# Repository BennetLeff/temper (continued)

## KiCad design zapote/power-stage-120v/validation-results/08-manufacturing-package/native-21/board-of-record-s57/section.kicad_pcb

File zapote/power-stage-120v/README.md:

# power-stage-120v: full-bridge induction power stage

> **Stale header (audit 2026-10-20):** the status and design text below predate the s53 board. Current: board s57 (25596d8e; FET holes 1.8 mm; `validation-results/08-manufacturing-package/native-21/fab/FAB-NOTE.md`), 290 × 190 mm, 2EDR8259X drivers, CA-IS3720HW isolators, PS1 deleted, KLDR025.TXP fuse, CT 1:200, U47 Schmitt buffer before U13.A. See DECISIONS.md items 75 and later (s54: item 81; s55: item 82; s56: item 85).

Status: **source compiled and audited; 240 × 160 mm four-layer placement
generated; native-06 routed and checked for renewed D4 review; physical NOT RUN.**
Design basis and justification: `docs/hardware/power-section-120v/` (POWER-SECTION.md,
LOSS-REFACTOR.md, COIL-MC.md). Front-end decision: `docs/adr/2026-09-25-front-end-architecture-brief.md`.

One board carries the mains entry, EMI filter, bridge rectifier and film bus, the full
bridge with both 2EDR8259X drivers next to the MOSFETs, the resonant capacitor bank and tank
current transformer, the DC-bus shoot-through OCP, isolated bus-voltage sense, the
thermal-cutoff-gated gate supply, and the SELV 15 V supply. The SELV controller (ESP32 plus the
integrated interlock, thermal-sense and RTD front end) connects through one SELV header (J4). Tank
over-current sensing is on this board (T1, U10–U13 → bus_fault); zapote/current-sense is a
bench-qualification unit only.

Native construction records: [progress](BUILD-PROGRESS.md),
[toolchain](TOOLCHAIN.md), [local footprints](FOOTPRINTS.md),
[earlier native results](NATIVE-02.md), [current routing](ROUTING.md),
[placement review](PLACEMENT-REVIEW.md), [oracle assessment](ORACLE-REVIEW.md),
[placement decisions](DECISIONS.md),
[return-current rules](RETURN-PATHS.md), and
[insulation preflight](RULES-PREFLIGHT.md). The revised 240 × 160 mm outline
and four layers are approved; the revised placement needs renewed D4 review.
D5 conditionally permits an 8.0 mm placement floor on
verified group IIIa-or-better laminate with one functional PE bond; insulation
qualification and airflow remain open. See [D5 basis](D5-BASIS.md).

## Build and verify

```sh
cd zapote/power-stage-120v
# 1. Compile (writes build/, which is gitignored)
uv tool run --offline --from "atopile==0.2.69" ato --non-interactive build \
    elec/src/power_stage_120v.ato:PowerStage120V
# 2. Per-instance part identity (vendored from harness-lab)
uv tool run --offline --from "atopile==0.2.69" python tools/circuit_export.py \
    "$PWD" "$PWD/build/resolved-components.json" \
    --entry-file elec/src/power_stage_120v.ato --entry PowerStage120V
# 3. Audit the fresh build, then (after a reviewed source change) freeze it
rustc --edition=2021 -O audit.rs -o /tmp/ps_audit
/tmp/ps_audit build/default.net build/default.csv build/resolved-components.json
cp build/default.net build/default.csv build/resolved-components.json frozen/
# 4. Mutation tests run against the frozen copies
rustc --edition=2021 --test audit.rs -o /tmp/ps_audit_t && /tmp/ps_audit_t
```

`frozen/` holds the reviewed build outputs. The netlist and resolved export embed absolute
source paths, so a rebuild elsewhere differs only in those paths. The netlist and BOM were
byte-identical, after path normalization, between two independent source snapshots (see the receipt).
`build-receipt.json` pins the hashes. Current result: 114 components, 75 nets. The audit
passes, and 48/48 tests pass, including deliberate miswires and the reference-bias regression.

**Part identity comes from `resolved-components.json` and the CSV, never from `default.net`.**
Atopile 0.2.69 writes a footprint-aliased part into the netlist's libsource field. In this
build, every 0603 resistor appears as `RC0603FR-071KL` and the LM4040 as `AO3400A`. The CSV BOM
and the per-instance resolved export are correct, and the audit cross-checks them for every
designator. `tools/circuit_export.py` is a verbatim copy of `harness-lab/circuit_export.py`
from `archive/rev38-power-entry-2026-09-25`.

## Fault interface

J4.10 now provides **BUS_FAULT**, low when both comparators are healthy and
high on either trip. U8 is a NAND; U9 is the default-high CA-IS3720HW.
This matches [the interlock's](../interlock/INTERFACES.md) active-high fault
contract without a polarity adapter. Input-side power loss defaults high
only with the output supply valid. HOT5 brownout, controller-supply loss,
return-wire faults and complete shutdown timing remain unqualified; see
[FAULT-INTERFACE.md](FAULT-INTERFACE.md).

## Controller header J4 (Molex Micro-Fit 3.0, 2x8, SELV)

| Pin | Net | Direction / meaning |
| ---: | --- | --- |
| 1 | BIAS_GOOD_J4 | Out: BIAS_GOOD (U40) through R146 220 k, high while the bias monitors are good and the heartbeat runs (stage 48, OPEN-ITEMS B13 H2). The controller must read it high-Z (≥ 1 MΩ pull-down). Was V15_SELV (PS1) until stage 38; the controller is powered through its J13 |
| 2, 4, 15 | SELV_GND | Return |
| 3 | V3V3 | In: controller 3.135–3.465 V rail matching the interlock contract; powers the SELV sides of U1, U2, U4, U9 |
| 5 / 6 | PWM_HA / PWM_LA | In: leg A high / low gate commands |
| 7 / 8 | PWM_HB / PWM_LB | In: leg B high / low (four independent signals allow phase-shift control) |
| 9 | PERMIT | In: active high. Low, floating or unpowered holds both drivers' DIS high (outputs off) |
| 10 | BUS_FAULT | Out: healthy low; high on shunt OCP (92.59 A nominal; 71.59–114.57 A at the release basis before the Kelvin shift, COMMISSIONING B2 / B3), bus OVP (272.64–287.45 V) or tank-CT over-current either polarity (73.19 A nominal, band 67.36–79.32 A, B9). U13 ORs the isolated bus fault with the tank-CT comparators on the SELV side. Fully unpowered HOT side defaults high while the controller supply is valid. |
| 11 / 12 | VBUS_P / VBUS_N | Out: AMC1311 differential output. V(P) − V(N) ≈ bus voltage / 120 (unity-gain amplifier; 198 V → 1.65 V; confirm gain and common-mode on the datasheet) |
| 13 | CT_ZC | Out: tank-current zero crossing (TLV3201 push-pull, 3.3 V logic). Undefined with no tank current: the controller must ignore it when idle |
| 14 | CT_MON | Out: biased tank-current waveform through 1 kΩ: 1.65 V + I_tank × 15 mV/A (1:200 into 3 Ω). The host input must be high impedance (≥ 10 MΩ assumed by the model) |
| 16 | LINE_ZC | Out: line zero crossing (U36 opto → U24 buffer, 3.3 V logic). Controller C49 reads it through 1 kΩ. Was SELV_GND in early stages. |

Required on the controller side (not on this board):
- the active-high-fault latch that drops PERMIT on BUS_FAULT high, tank OCP, over-temperature or a watchdog timeout
- phase control from CT_ZC that inhibits switching before the tank goes capacitive (the comparator is on this board; the inhibit logic is not)
- integration respecting the single functional PE bond implemented on this board

## Domains and barrier

HOT reference is `LEG_RET`, the leg side of the 1 mΩ shunt; layout must star it at shunt pad 2.
Only these parts may cross HOT↔SELV, and the audit enforces each pin's side:

- Infineon 2EDR8259X (U1, U2; UCC21550 until stage 28, DECISIONS 31)
- AMC1311 (U4)
- CA-IS3720HW (U9, U32)
- VOL628A-2X001T (U36, line zero-cross; mains to SELV)
- CST3015-200ED (T1)

PS1 (IRM-20-15) was deleted at stage 38. U41 / U42 (R24C2T25) and U43 / U44 (ISO6721FB) are HOT-to-HOT.

The controller return has one removable functional 0 Ω PE link. It is not
a protective-earth path and does not waive HOT-to-controller insulation.

Provisional creepage and clearance rules are applied to the routed board. The full-bridge differential
RMS and peak voltages across each barrier remain unverified; the historical
tank peak is not a sufficient basis for selecting creepage bands. See
[RULES-PREFLIGHT.md](RULES-PREFLIGHT.md).

## Safety chain implemented in hardware

| Fault | Path |
| --- | --- |
| Hard short or bridge failure | F1 25 A time-delay ceramic (Eaton Bussmann MDA-25-R: 10 kA @ 125 Vac, 1.5 kA @ 250 Vac) in 30 A 01220088Z clips |
| Shoot-through / MOSFET short | 1 mΩ DC-return shunt → TLV3201 (nominal 92.59 A) → NAND gate → CA-IS3720HW → BUS_FAULT high → interlock latch → PERMIT low → DIS |
| Elevated DC bus | Bus divider → TLV3201 (272.64–287.45 V) → NAND gate → CA-IS3720HW → BUS_FAULT high → interlock latch → PERMIT low → DIS; this inhibits restart but does not clamp bus voltage |
| Tank over-current / pan fault | CT (T1) → on-board comparators U10/U11, ORed with the bus fault in U13 → bus_fault → controller interlock latch |
| Heatsink or glass over-temperature | Off-board Microtemp cutoffs in the J3 loop open the IRM-05-15 input: gate drive and HOT 5 V drop; BUS_FAULT defaults high if controller 3.3 V remains valid. No electronics or firmware involved |
| Controller hang / reset | Interlock-board watchdog; PERMIT floating = disabled |
| Gate-supply loss | 2EDR8259X UVLO and active output clamp hold outputs low; 10 kΩ gate-source hold-off |
| Line surge | TMOV20RP175E (175 Vrms, 455 V clamp) ahead of 650 V MOSFETs |

## Open before fabrication and powered qualification

1. **Coil measurement** (COIL-MC.md). Sets the resonant bank value (0.54 µF now, for 70 µH / 32 kHz), CT burden and frequency limits.
2. **Parts to confirm against manufacturer drawings:**
   - J1 is Phoenix 1714971 (MKDS 5/2-9,5, UL/CSA group B 30 A; stage 27) for L/N only; J6 is a Phoenix 1704004 PE branch from the chassis stud. J2/J5 and the four disconnect terminals use Würth 74650074; assembly, temperature and spacing qualification remain open.
   - ~~Littelfuse 102071 clip current rating~~ (10 A): replaced by 30 A 01220088Z clips. The fuse is now Eaton Bussmann MDA-25-R (25 A, 10 kA @ 125 Vac), DECISIONS.md 2026-10-08
   - ~~TDK B82726S2203A020 pin numbering~~ (confirmed from datasheet 2026-09-25: windings 1-4, 2-3)
   - ~~Molex 0430451612 order code~~: a real, current Micro-Fit 3.0 2×8 vertical part that matches the footprint and pinout. Its mate is 43025-1600 + 43030-0007 (`validation-results/08-manufacturing-package/native-21/owner-items/order/ORDER-PACKAGE.md` §1c). Only the post-hole check against Molex drawing 430451612_sd is left
   - 942C AC voltage rating vs frequency (≈ 236 V rms at line crest, 35 kHz): CDE's 1200 Vdc curves (942C.pdf p.4) have no 0.22 µF trace. The 0.33 µF trace allows ≈ 270 V rms at 35 kHz (read from the plot), and the smaller value allows more, so it passes at 25 °C. The hot-spot rating stays a bench item
3. **Footprint qualification:** all current local footprints are now
   in `libraries/`. [FOOTPRINTS.md](FOOTPRINTS.md) records their drawing
   references and provisional formed-lead, retention and assembly limits.
4. **Under-glass cutoff rating:** needs a glass-underside temperature measurement at the 482 °F setpoint; heatsink cutoff about 120 °C, from available G4A ratings.
5. **Bench:** dead time (39 kΩ ≈ 348 ns nominal), gate resistors, snubber value, OCP trip calibration, ZVS at light load.

Physical assembly, powered test, EMI, insulation and certification: **NOT RUN**.

The release gates (two tiers: bench prototype lot vs mains-connected / product release) are in
`validation-results/08-manufacturing-package/native-21/fab/FAB-NOTE.md`. The owner decisions M6, M10
and M11 are in DECISIONS.md (2026-10-08). The integrated SELV controller that drives J4 is captured in
`zapote/controller/`.

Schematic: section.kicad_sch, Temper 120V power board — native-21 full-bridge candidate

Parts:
BR1: GBJ2510-F; Diode_Bridge_GBJ2510
C1, C2: R463N410050N1K; KEMET_R463N410000N1M_P22.50_ReviewOnly
C3, C4: DE1E3RA222MJ4BH01F; Murata_DE1E3RA222MA4BP01F_P10.0_Pad1.5_ReviewOnly
C5, C6: B32676G1905K000; TDK_B32656G0275J000_4Pin_P37.50_P20.30_ReviewOnly
C7, C14, C25, C28, C29, C32, C34, C35, C36, C37, C44, C45, C46, C47, C48, C49, C54, C61, C65, C70, C74, C75, C80, C81, C82, C87, C89, C131, C133, C134, C135, C139, C144, C153, C154, C155, C156, C157, C158, C159, C160, C161, C163, C168, C169, C170, C171, C172, C173, C174, C175, C176, C177, C178, C179: CC0603KRX7R9BB104; C_0603_1608Metric
C8, C10, C15, C17: CC0805KRX7R9BB104; C_0805_2012Metric
C9, C16, C24, C26, C90, C91, C92, C93, C94, C95, C96, C97, C98, C99, C100, C102, C103, C104, C106, C107, C108, C132, C136, C140: CL32B106KBJNNNE; C_1210_3225Metric
C11, C18: GRM21BZ71E106KE15L; C_0805_2012Metric
C12, C13, C19, C20: CC1206JKNPOCBN102; C_1206_3216Metric
C21, C22, C23, C151, C152: B32643H8104J000; Bank_Film_DualPitch_P22.5_P27.5_Radial
C27, C31, C33, C66, C67, C68, C69, C76, C77, C78, C79, C83, C84, C85, C86, C164, C165, C166: C0603C102J5GACTU; C_0603_1608Metric
C30, C167: CL10C101JB8NNNC; C_0603_1608Metric
C38, C39, C40, C41: B32652A0104K000; TDK_B32652A0104K000_P15.00_ReviewOnly
C42, C43: GRM31C5C1H104JA01L; C_1206_3216Metric
C50, C51, C52, C53, C57, C58, C59, C60, C64: GRM188R71E105KA12D; C_0603_1608Metric
C55, C56, C62, C63: GRM1885C1H472JA01D; C_0603_1608Metric
C71, C72, C105, C109, C162: CL10C331JB8NNNC; C_0603_1608Metric
C110, C111, C112, C113, C114, C115, C116, C117, C118, C119, C120, C121, C122, C123, C124, C125: CL05B104KB54PNC; C_0402_1005Metric
C126, C127, C128, C129: 6SVPC220MV; CP_Elec_6.3x5.9
C145, C146, C147, C148, C149, C150: CL21B105KBFNNNE; C_0805_2012Metric
D3, D17: 30KPA150CA; P600_Axial_P12.70mm_ReviewOnly
D4, D5: BAS116H,115; D_SOD-123F
D6, D7, D8, D9: PMEG6030EP,115; D_SOD-128
D18, D19, D20: BAT54S-7-F; SOT-23
F1: KLDR025.TXP; Fuseholder_Clip-10.3x38mm_Littelfuse_125_Inline_P41.76x10.8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
F2: 3403.0279.23; Fuse_Schurter_UMT-H_15.4x5.35mm
J1: 1714971; Phoenix_MKDS-5-2-9.52_1714971
J2, J5: 7466004R; Wuerth_REDCUBE-SMT_WP-SMBU_7466004R
J3, J11: B2P3-VH(LF)(SN); JST_VH_B2P3-VH_1x02_P7.92mm_Vertical
J4: 0430451612; Molex_Micro-Fit_3.0_43045-1612_2x08_P3.00mm_Vertical
J6: 1704004; Phoenix_KDS3_1704004_1Pos_2Pin_ReviewOnly
L1: B82726S2243A020; B82726S2_ReviewOnly
PS2: MPM-20-24; Converter_ACDC_MeanWell_IRM-20-xx_THT
Q2, Q3, Q5, Q6: IPW65R018CFD7; TO-247-3_Vertical_D1.8
R1, R2: 1206W4F1003T5E; R_1206_3216Metric
R3, R4, R146: RC1206FR-07220KL; R_1206_3216Metric
R5: CSS2H-2512R-1L00F; R_Shunt_Bourns_CSS2H-2512_Kelvin
R6, R14: 0603WAF1000T5E; R_0603_1608Metric
R7, R15, R62, R128, R135, R136, R138, R140, R142: 0603WAF1003T5E; R_0603_1608Metric
R9, R17, R133: RT0603BRD0749K9L; R_0603_1608Metric
R10, R12, R18, R20: PS122WF680JT4E; R_2512_6332Metric
R11, R13, R19, R21, R73, R76, R91, R109, R124: 0603WAF1002T5E; R_0603_1608Metric
R22, R23, R24, R25, R26, R27, R28, R29: RC1206FR-07470KL; R_1206_3216Metric
R30: RT0603BRD0715K8L; R_0603_1608Metric
R31: 0603WAF5601T5E; R_0603_1608Metric
R32, R36, R49, R50, R78, R80, R82, R84, R96, R98, R100, R102, R111, R113, R115, R117: RT0603BRD0710KL; R_0603_1608Metric
R33: RT0603BRD077K5L; R_0603_1608Metric
R34, R127, R129: RT0603BRD0716KL; R_0603_1608Metric
R35, R44, R45, R61, R86, R88, R93, R104, R106, R119, R121: RT0603BRD0711KL; R_0603_1608Metric
R37: RT0603BRD07140KL; R_0603_1608Metric
R38: 0603WAF0000T5E; R_0603_1608Metric
R39: RC1206FR-073RL; R_1206_3216Metric
R40, R41: RT0603BRD071KL; R_0603_1608Metric
R42: 1206W4F1001T5E; R_1206_3216Metric
R43, R46: RT0603BRD072K21L; R_0603_1608Metric
R47, R134: 0603WAF1001T5E; R_0603_1608Metric
R48: RT0603BRD07105KL; R_0603_1608Metric
R51, R52, R55, R56: RL1206FR-070R68L; R_1206_3216Metric
R53, R54, R57, R58: 1206W4F100KT5E; R_1206_3216Metric
R59, R63, R65: RC1206FR-072K2L; R_1206_3216Metric
R67, R68, R69, R70: RC1206FR-0716K5L; R_1206_3216Metric
R71, R72, R74, R75, R131: ERJ-PA3F4991V; R_0603_1608Metric
R77, R95, R110: RT0603BRD076K2L; R_0603_1608Metric
R79, R97, R112: RT0603BRD074K42L; R_0603_1608Metric
R81, R99, R114: RT0603BRD07750RL; R_0603_1608Metric
R83, R101, R116: RT0603BRD072K94L; R_0603_1608Metric
R85, R103, R118: RT0603BRD0790K9L; R_0603_1608Metric
R87, R105, R120: RT0603BRD07104KL; R_0603_1608Metric
R92, R94, R144: RT0603BRD0763K4L; R_0603_1608Metric
R125: 0603WAF3302T5E; R_0603_1608Metric
R130: AC05000001507JAC00; R_Axial_Vishay_AC05_D7.5mm_P5.08mm_Vertical
R132: 0603WAF2200T5E; R_0603_1608Metric
R137, R139, R141, R143: 0603WAF2702T5E; R_0603_1608Metric
R145: TNPW060311K7BEEA; R_0603_1608Metric
RV1: TMOV20RP175E; TMOV20RP_ReviewOnly
T1: CST3015-200ED; CST3015
U1, U2: 2EDR8259XXUMA1; SOIC16W_Isolated
U3, U37, U38, U39: TPS70950QDBVRQ1; SOT-23-5
U4: AMC1311BDWVR; SOIC-8_7.5x5.85mm_P1.27mm
U5: LM4050AEM3-2.5/NOPB; SOT-23
U6, U7, U10, U11, U12: TLV3201AIDBVR; SOT-23-5
U8: SN74LVC1G10DBVR; SOT-23-6
U9, U32: CA-IS3720HW; SOIC16W_DW0016B_HV
U13: SN74LVC1G332DBVR; SOT-23-6
U14: TPS3700DDCR; SOT-23-6
U15, U24, U40, U47: SN74LVC1G17DBVR; SOT-23-5
U16, U18, U20: TLVH431BQDBZR; SOT-23
U17, U19, U21: TL431BQDBZR; SOT-23
U22, U23: SN74LVC1G00DBVR; SOT-23-5
U26: TPS7A4700RGWR; Texas_RGW0020A_VQFN-20-1EP_5x5mm_P0.65mm_EP3.15x3.15mm
U29, U30, U31: LM2901BIDR; SOIC-14_3.9x8.7mm_P1.27mm
U36: VOL628A-2X001T; VOL628A_LSOP4_ReviewOnly
U41, U42: R24C2T25/R-R; RECOM_SSOP-36_7.5x12.83mm_P0.65mm_ReviewOnly
U43, U44: ISO6721FBDR; SOIC-8_3.9x4.9mm_P1.27mm
U45, U46: SN74LVC1G132DBVR; SOT-23-5

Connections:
ac_l_in: F1.1 (p1), J1.1 (p1)
ac_n_in: C1.2 (p2), J1.2 (p2), L1.2 (p2), R2.2 (p2), RV1.2 (p2)
bias_good: R146.1 (p1), U22.2 (p2), U23.2 (p2), U40.4 (Y); also elsewhere on the board
bias_good_j4: J4.1 (p1), R146.2 (p2)
bias_ha-en: R62.2 (p2), R127.1 (p1), U41.4 (p4)
bias_ha-fbm: C71.1 (p1), R92.2 (p2), R93.1 (p1), U41.33 (p33), U41.34 (p34)
bias_ha-outa_nc: U43.2 (p2)
bias_ha.iso-p3: U41.3 (p3)
bias_ha.iso-p32: U41.32 (p32)
bias_ha.monitor-good: R109.2 (p2), U30.1 (OUT2), U30.2 (OUT1), U30.13 (OUT4), U30.14 (OUT3), U43.3 (p3)
bias_ha.monitor-halfref: R97.2 (p2), R98.1 (p1), U30.5 (IN1+), U30.6 (IN2-), U30.8 (IN3-), U30.11 (IN4+)
bias_ha.monitor-ldo_en: R140.2 (p2), R141.1 (p1), U38.3 (EN)
bias_ha.monitor-ov: C77.1 (p1), R101.2 (p2), R102.1 (p1), U30.4 (IN1-); also elsewhere on the board
bias_ha.monitor-ref: R63.2 (p2), R97.1 (p1), U19.1 (K), U19.2 (REF)
bias_ha.monitor-spanov: C79.1 (p1), R105.2 (p2), R106.1 (p1), U30.10 (IN4-); also elsewhere on the board
bias_ha.monitor-spanuv: C78.1 (p1), R103.2 (p2), R104.1 (p1), U30.9 (IN3+); also elsewhere on the board
bias_ha.monitor-uv: C76.1 (p1), R99.2 (p2), R100.1 (p1), U30.7 (IN2+); also elsewhere on the board
bias_ha.monitor-v5: C136.1 (p1), C157.1 (p1), R109.1 (p1), U38.5 (OUT), U43.1 (p1)
bias_ha.monitor.ldo5-nc: U38.4 (NC)
bias_ha.split-fb: R95.2 (p2), R96.1 (p1), U18.1 (REF)
bias_hb-en: R128.2 (p2), R129.1 (p1), U42.4 (p4)
bias_hb-fbm: C72.1 (p1), R61.1 (p1), R94.2 (p2), U42.33 (p33), U42.34 (p34)
bias_hb-outa_nc: U44.2 (p2)
bias_hb.iso-p3: U42.3 (p3)
bias_hb.iso-p32: U42.32 (p32)
bias_hb.monitor-good: R124.2 (p2), U31.1 (OUT2), U31.2 (OUT1), U31.13 (OUT4), U31.14 (OUT3), U44.3 (p3)
bias_hb.monitor-halfref: R112.2 (p2), R113.1 (p1), U31.5 (IN1+), U31.6 (IN2-), U31.8 (IN3-), U31.11 (IN4+)
bias_hb.monitor-ldo_en: R142.2 (p2), R143.1 (p1), U39.3 (EN)
bias_hb.monitor-ov: C84.1 (p1), R116.2 (p2), R117.1 (p1), U31.4 (IN1-); also elsewhere on the board
bias_hb.monitor-ref: R65.2 (p2), R112.1 (p1), U21.1 (K), U21.2 (REF)
bias_hb.monitor-spanov: C86.1 (p1), R120.2 (p2), R121.1 (p1), U31.10 (IN4-); also elsewhere on the board
bias_hb.monitor-spanuv: C85.1 (p1), R118.2 (p2), R119.1 (p1), U31.9 (IN3+); also elsewhere on the board
bias_hb.monitor-uv: C83.1 (p1), R114.2 (p2), R115.1 (p1), U31.7 (IN2+); also elsewhere on the board
bias_hb.monitor-v5: C140.1 (p1), C159.1 (p1), R124.1 (p1), U39.5 (OUT), U44.1 (p1)
bias_hb.monitor.ldo5-nc: U39.4 (NC)
bias_hb.split-fb: R110.2 (p2), R111.1 (p1), U20.1 (REF)
bias_ls-fb: R77.2 (p2), R78.1 (p1), U16.1 (REF)
blw_l: F2.2 (p2), R130.1 (p1)
blw_lr: J11.1 (p1), R130.2 (p2)
bus_fault: J4.10 (p10), U13.4 (Y); also elsewhere on the board
bus_fault_flt: C167.1 (p1), R134.2 (p2), U47.2 (A)
bus_fault_hot: U8.4 (Y), U9.4 (p4); also elsewhere on the board
bus_fault_iso: R134.1 (p1), U9.13 (p13)
bus_fault_st: U13.1 (A), U47.4 (Y)
bus_p: BR1.1 (PLUS), C5.1 (p1), C5.2 (p2), C6.1 (p1), C6.2 (p2), C12.1 (p1), C19.1 (p1), C38.1 (p1), C39.1 (p1), C40.1 (p1), C41.1 (p1), D3.1 (p1), Q2.2 (D), Q5.2 (D), R3.1 (p1), R26.1 (p1)
busbleed_mid: D3.2 (p2), D17.1 (p1), R3.2 (p2), R4.1 (p1)
coil_feed: J2.1, T1.2 (p2)
crbleed_1: R22.2 (p2), R23.1 (p1)
crbleed_2: R23.2 (p2), R24.1 (p1)
crbleed_3: R24.2 (p2), R25.1 (p1)
ct_mon: J4.14 (p14), R47.2 (p2); also elsewhere on the board
ct_oc_neg: U11.1 (OUT), U13.6 (C)
ct_oc_pos: U10.1 (OUT), U13.3 (B)
ct_ref_hi: R43.2 (p2), R44.1 (p1), U10.4 (INN)
ct_ref_lo: R45.2 (p2), R46.1 (p1), U11.3 (INP)
ct_s1: C42.1 (p1), R39.1 (p1), R42.1 (p1), T1.3 (p3)
ct_s2: C42.2 (p2), C43.1 (p1), R39.2 (p2), R40.2 (p2), R41.1 (p1), T1.4 (p4), U12.4 (INN)
ct_sense_mon: D4.2 (A), D5.1 (K), R42.2 (p2), R47.1 (p1), U10.3 (INP), U11.4 (INN), U12.3 (INP)
ct_zc: J4.13 (p13), U12.1 (OUT); also elsewhere on the board
hb.iso-nc2: U32.2 (p2)
hb.iso-nc5: U32.5 (p5)
hb.iso-nc6: U32.6 (p6)
hb.iso-nc8: U32.8 (p8)
hb.iso-nc10: U32.10 (p10)
hb.iso-nc11: U32.11 (p11)
hb.iso-nc12: U32.12 (p12)
hb.iso-nc15: U32.15 (p15)
hb_bufo: R132.1 (p1), U46.4 (p4)
hb_hold: C166.1 (p1), D19.2 (p2), R133.1 (p1), U40.2 (A)
hb_m: C164.2 (p2), C165.1 (p1)
hb_rc: C162.1 (p1), R131.2 (p2), U45.2 (p2)
hb_rx: U32.13 (p13), U46.2 (p2)
hb_s: C164.1 (p1), R132.2 (p2)
hb_tx: R131.1 (p1), U32.4 (p4), U45.4 (p4)
hb_x: C165.2 (p2), D19.3 (p3)
hot5: C26.1 (p1), C28.1 (p1), C32.1 (p1), C34.1 (p1), C35.1 (p1), C36.1 (p1), C48.1 (p1), C49.1 (p1), C149.1 (p1), R31.1 (p1), R48.1 (p1), R50.1 (p1), U3.5 (OUT), U4.1 (VDD1), U6.5 (VCC), U7.5 (VCC), U8.5 (VCC), U9.3 (p3), U14.5 (VDD), U15.5 (VCC); also elsewhere on the board
hot5_en: R136.2 (p2), R137.1 (p1), U3.3 (EN)
hot5_ok_hot: U8.6 (C), U15.4 (Y)
hot5_uv_raw: R50.2 (p2), U14.1 (OUTA), U14.6 (OUTB), U15.2 (A)
hot5_uv_sense: R48.2 (p2), R49.1 (p1), U14.3 (INA)
hsb_good: R135.2 (p2), U46.1 (p1)
hv_ret: BR1.4 (MINUS), C5.3 (p3), C5.4 (p4), C6.3 (p3), C6.4 (p4), C38.2 (p2), C39.2 (p2), C40.2 (p2), C41.2 (p2), D17.2 (p2), R4.2 (p2), R5.4 (p4)
l_f: C1.1 (p1), F1.2 (p2), L1.1 (p1), R1.1 (p1), RV1.1 (p1)
l_filt: BR1.2 (AC1), C2.1 (p1), C3.1 (p1), F2.1 (p1), J3.1 (p1), L1.4 (p4), R67.1 (p1)
ldo_nr: C64.1 (p1), U26.14 (p14)
led1: R68.2 (p2), U36.1 (p1)
led2: R69.1 (p1), U36.2 (p2)
leg_a-driver_dis: R73.2 (p2), U1.5 (p5), U22.4 (p4)
leg_a-gate_h: C55.1 (p1), D6.2 (p2), Q2.1 (G), R10.2 (p2), R11.1 (p1)
leg_a-gate_l: C56.1 (p1), D7.2 (p2), Q3.1 (G), R12.2 (p2), R13.1 (p1)
leg_a-off_h: D6.1 (p1), R53.1 (p1)
leg_a-off_l: D7.1 (p1), R54.1 (p1)
leg_a-out_h: R10.1 (p1), R53.2 (p2), U1.15 (p15)
leg_a-out_l: R12.1 (p1), R54.2 (p2), U1.10 (p10); also elsewhere on the board
leg_a-permit_gate: R6.2 (p2), R7.1 (p1), U22.1 (p1)
leg_a.bias_h-damp: C126.1 (p1), R51.2 (p2)
leg_a.bias_l-damp: C127.1 (p1), R52.2 (p2)
leg_a.driver-dt: R9.1 (p1), U1.6 (p6)
leg_a.driver-nc_7: U1.7 (p7)
leg_b-driver_dis: R76.2 (p2), U2.5 (p5), U23.4 (p4); also elsewhere on the board
leg_b-gate_h: C62.1 (p1), D8.2 (p2), Q5.1 (G), R18.2 (p2), R19.1 (p1)
leg_b-gate_l: C63.1 (p1), D9.2 (p2), Q6.1 (G), R20.2 (p2), R21.1 (p1)
leg_b-off_h: D8.1 (p1), R57.1 (p1)
leg_b-off_l: D9.1 (p1), R58.1 (p1)
leg_b-out_h: R18.1 (p1), R57.2 (p2), U2.15 (p15)
leg_b-out_l: R20.1 (p1), R58.2 (p2), U2.10 (p10)
leg_b-permit_gate: R14.2 (p2), R15.1 (p1), U23.1 (p1)
leg_b.bias_h-damp: C128.1 (p1), R55.2 (p2)
leg_b.bias_l-damp: C129.1 (p1), R56.2 (p2)
leg_b.driver-dt: R17.1 (p1), U2.6 (p6)
leg_b.driver-nc_7: U2.7 (p7)
leg_ret: C13.2 (p2), C20.2 (p2), C52.1 (p1), C53.1 (p1), C56.2 (p2), C59.1 (p1), C60.1 (p1), C63.2 (p2), C92.1 (p1), C93.1 (p1), C96.1 (p1), C97.1 (p1), C114.1 (p1), C115.1 (p1), C116.1 (p1), C117.1 (p1), C122.1 (p1), C123.1 (p1), C124.1 (p1), C125.1 (p1), Q3.3 (S), Q6.3 (S), R5.1 (p1), R13.2 (p2), R21.2 (p2), R52.1 (p1), R56.1 (p1), R72.2 (p2), R75.2 (p2), R77.1 (p1), R81.1 (p1), R83.1 (p1), U16.2 (K); also elsewhere on the board
line_zc: J4.16 (p16), U24.4 (Y)
line_zc.buffer-nc: U24.1 (NC)
line_zc_raw: R125.2 (p2), U24.2 (A), U36.4 (p4)
ls_v5: C132.1 (p1), C133.1 (p1), C158.1 (p1), C160.1 (p1), C161.1 (p1), R91.1 (p1), U32.3 (p3), U37.5 (OUT), U43.8 (p8), U44.8 (p8), U45.5 (p5)
mon_good_ha: D18.3 (p3), U43.6 (p6)
mon_good_hb: D20.2 (p2), U44.6 (p6)
monitor_ls-good: D18.1 (p1), D20.3 (p3), R91.2 (p2), U29.1 (OUT2), U29.2 (OUT1), U29.13 (OUT4), U29.14 (OUT3), U45.1 (p1)
monitor_ls-halfref: R79.2 (p2), R80.1 (p1), U29.5 (IN1+), U29.6 (IN2-), U29.8 (IN3-), U29.11 (IN4+)
monitor_ls-ldo_en: R138.2 (p2), R139.1 (p1), U37.3 (EN)
monitor_ls-ov: C67.1 (p1), R83.2 (p2), R84.1 (p1), U29.4 (IN1-)
monitor_ls-ref: R59.2 (p2), R79.1 (p1), U17.1 (K), U17.2 (REF)
monitor_ls-spanov: C69.1 (p1), R87.2 (p2), R88.1 (p1), U29.10 (IN4-); also elsewhere on the board
monitor_ls-spanuv: C68.1 (p1), R85.2 (p2), R86.1 (p1), U29.9 (IN3+); also elsewhere on the board
monitor_ls-uv: C66.1 (p1), R81.2 (p2), R82.1 (p1), U29.7 (IN2+); also elsewhere on the board
monitor_ls.ldo5-nc: U37.4 (NC)
n_filt: BR1.3 (AC2), C2.2 (p2), C4.1 (p1), J11.2 (p2), L1.3 (p3), PS2.2 (p2), R70.2 (p2)
n_ha: C10.2 (p2), C11.2 (p2), C50.2 (p2), C51.2 (p2), C71.2 (p2), C75.2 (p2), C76.2 (p2), C77.2 (p2), C78.2 (p2), C79.2 (p2), C80.2 (p2), C90.2 (p2), C91.2 (p2), C104.2 (p2), C110.2 (p2), C111.2 (p2), C112.2 (p2), C113.2 (p2), C126.2 (p2), C135.2 (p2), C136.2 (p2), C145.2 (p2), C157.2 (p2), R93.2 (p2), R96.2 (p2), R98.2 (p2), R100.2 (p2), R102.2 (p2), R104.2 (p2), R106.2 (p2), R141.2 (p2), U1.14 (p14), U18.3 (A), U19.3 (A), U30.12 (GND), U38.2 (GND), U41.19 (p19), U41.20 (p20), U41.21 (p21), U41.22 (p22), U41.23 (p23), U41.24 (p24), U41.25 (p25), U41.26 (p26), U41.27 (p27), U41.30 (p30), U41.31 (p31), U41.35 (p35), U41.36 (p36), U43.4 (p4); also elsewhere on the board
n_hb: C17.2 (p2), C18.2 (p2), C57.2 (p2), C58.2 (p2), C72.2 (p2), C82.2 (p2), C83.2 (p2), C84.2 (p2), C85.2 (p2), C86.2 (p2), C87.2 (p2), C94.2 (p2), C95.2 (p2), C108.2 (p2), C118.2 (p2), C119.2 (p2), C120.2 (p2), C121.2 (p2), C128.2 (p2), C139.2 (p2), C140.2 (p2), C147.2 (p2), C159.2 (p2), R61.2 (p2), R111.2 (p2), R113.2 (p2), R115.2 (p2), R117.2 (p2), R119.2 (p2), R121.2 (p2), R143.2 (p2), U2.14 (p14), U20.3 (A), U21.3 (A), U31.12 (GND), U39.2 (GND), U42.19 (p19), U42.20 (p20), U42.21 (p21), U42.22 (p22), U42.23 (p23), U42.24 (p24), U42.25 (p25), U42.26 (p26), U42.27 (p27), U42.30 (p30), U42.31 (p31), U42.35 (p35), U42.36 (p36), U44.4 (p4); also elsewhere on the board
n_ls: C8.2 (p2), C9.2 (p2), C15.2 (p2), C16.2 (p2), C24.2 (p2), C52.2 (p2), C53.2 (p2), C59.2 (p2), C60.2 (p2), C64.2 (p2), C65.2 (p2), C66.2 (p2), C67.2 (p2), C68.2 (p2), C69.2 (p2), C70.2 (p2), C74.2 (p2), C81.2 (p2), C92.2 (p2), C93.2 (p2), C96.2 (p2), C97.2 (p2), C98.2 (p2), C99.2 (p2), C100.2 (p2), C102.2 (p2), C103.2 (p2), C105.2 (p2), C106.2 (p2), C107.2 (p2), C109.2 (p2), C114.2 (p2), C115.2 (p2), C116.2 (p2), C117.2 (p2), C122.2 (p2), C123.2 (p2), C124.2 (p2), C125.2 (p2), C127.2 (p2), C129.2 (p2), C131.2 (p2), C132.2 (p2), C133.2 (p2), C146.2 (p2), C148.2 (p2), C158.2 (p2), C160.2 (p2), C161.2 (p2), C162.2 (p2), PS2.3 (p3), R78.2 (p2), R80.2 (p2), R82.2 (p2), R84.2 (p2), R86.2 (p2), R88.2 (p2), R127.2 (p2), R129.2 (p2), R139.2 (p2), U1.9 (p9), U2.9 (p9), U16.3 (A), U17.3 (A), U26.4 (p4), U26.5 (p5), U26.7 (p7), U26.8 (p8), U26.9 (p9), U26.10 (p10), U26.21 (p21), U29.12 (GND), U32.1 (p1), U32.7 (p7), U37.2 (GND), U41.1 (p1), U41.2 (p2), U41.5 (p5), U41.8 (p8), U41.9 (p9), U41.10 (p10), U41.11 (p11), U41.12 (p12), U41.13 (p13), U41.14 (p14), U41.15 (p15), U41.16 (p16), U41.17 (p17), U41.18 (p18), U42.1 (p1), U42.2 (p2), U42.5 (p5), U42.8 (p8), U42.9 (p9), U42.10 (p10), U42.11 (p11), U42.12 (p12), U42.13 (p13), U42.14 (p14), U42.15 (p15), U42.16 (p16), U42.17 (p17), U42.18 (p18), U43.5 (p5), U43.7 (p7), U44.5 (p5), U44.7 (p7), U45.3 (p3); also elsewhere on the board
ocp_kelvin_n: R5.3 (p3), R33.2 (p2)
ocp_kelvin_p: C25.2 (p2), C26.2 (p2), C27.2 (p2), C28.2 (p2), C30.2 (p2), C31.2 (p2), C32.2 (p2), C33.2 (p2), C34.2 (p2), C35.2 (p2), C36.2 (p2), C48.2 (p2), C49.2 (p2), C149.2 (p2), R5.2 (p2), R30.2 (p2), R35.2 (p2), R37.2 (p2), R49.2 (p2), R137.2 (p2), R145.2 (p2), U3.2 (GND), U4.3 (SHTDN), U4.4 (GND1), U5.2 (A), U6.2 (GND), U7.2 (GND), U8.2 (GND), U9.1 (p1), U9.7 (p7), U14.2 (GND), U15.3 (GND); also elsewhere on the board
ocp_node: C30.1 (p1), R32.2 (p2), R33.1 (p1), U6.3 (INP); also elsewhere on the board
ocp_ok_hot: U6.1 (OUT), U8.1 (A)
ocp_thresh: C31.1 (p1), R34.2 (p2), R35.1 (p1), U6.4 (INN)
ovp_ok_hot: U7.1 (OUT), U8.3 (B)
ovp_thresh: C33.1 (p1), R36.2 (p2), R37.1 (p1), U7.3 (INP)
p2: U26.2 (p2)
p6: U26.6 (p6)
p11: U26.11 (p11)
p12: U26.12 (p12)
p17: U26.17 (p17)
p18: U26.18 (p18)
p19: U26.19 (p19)
p_ha: C10.1 (p1), C11.1 (p1), C75.1 (p1), C80.1 (p1), C104.1 (p1), C135.1 (p1), C145.1 (p1), R63.1 (p1), R71.1 (p1), R92.1 (p1), R103.1 (p1), R105.1 (p1), R140.1 (p1), U1.16 (p16), U30.3 (VCC), U38.1 (IN), U41.28 (p28), U41.29 (p29); also elsewhere on the board
p_hb: C17.1 (p1), C18.1 (p1), C82.1 (p1), C87.1 (p1), C108.1 (p1), C139.1 (p1), C147.1 (p1), R65.1 (p1), R74.1 (p1), R94.1 (p1), R118.1 (p1), R120.1 (p1), R142.1 (p1), U2.16 (p16), U31.3 (VCC), U39.1 (IN), U42.28 (p28), U42.29 (p29); also elsewhere on the board
pe: C3.2 (p2), C4.2 (p2), J6.1 (p1), J6.2 (p2), R38.1 (p1)
permit: J4.9 (p9), R6.1 (p1), R14.1 (p1), R135.1 (p1); also elsewhere on the board
pwm_ha: J4.5 (p5), U1.1 (p1); also elsewhere on the board
pwm_hb: J4.7 (p7), U2.1 (p1); also elsewhere on the board
pwm_la: J4.6 (p6), U1.2 (p2); also elsewhere on the board
pwm_lb: J4.8 (p8), U2.2 (p2); also elsewhere on the board
r1mid: R67.2 (p2), R68.1 (p1)
r2mid: R69.2 (p2), R70.1 (p1)
ref25: R31.2 (p2), R32.1 (p1), R34.1 (p1), R36.1 (p1), R144.1 (p1), U5.1 (K); also elsewhere on the board
ref25_wd: R144.2 (p2), R145.1 (p1), U14.4 (INB)
res_a: C21.1 (p1), C22.1 (p1), C23.1 (p1), C151.1 (p1), C152.1 (p1), J5.1, R22.1 (p1)
selv_gnd: C7.2 (p2), C14.2 (p2), C29.2 (p2), C37.2 (p2), C43.2 (p2), C44.2 (p2), C45.2 (p2), C46.2 (p2), C47.2 (p2), C54.2 (p2), C61.2 (p2), C89.2 (p2), C134.2 (p2), C144.2 (p2), C150.2 (p2), C153.2 (p2), C154.2 (p2), C155.2 (p2), C156.2 (p2), C163.2 (p2), C166.2 (p2), C167.2 (p2), C168.2 (p2), C169.2 (p2), C170.2 (p2), C171.2 (p2), C172.2 (p2), C173.2 (p2), C174.2 (p2), C175.2 (p2), C176.2 (p2), C177.2 (p2), C178.2 (p2), C179.2 (p2), D5.2 (A), D19.1 (p1), J4.2 (p2), J4.4 (p4), J4.15 (p15), R7.2 (p2), R9.2 (p2), R15.2 (p2), R17.2 (p2), R38.2 (p2), R41.2 (p2), R44.2 (p2), R46.2 (p2), R133.2 (p2), U1.4 (p4), U2.4 (p4), U4.5 (GND2), U9.9 (p9), U9.16 (p16), U10.2 (GND), U11.2 (GND), U12.2 (GND), U13.2 (GND), U22.3 (p3), U23.3 (p3), U24.3 (GND), U32.9 (p9), U32.16 (p16), U36.3 (p3), U40.3 (GND), U46.3 (p3), U47.3 (GND); also elsewhere on the board
sw_a: C12.2 (p2), C13.1 (p1), C50.1 (p1), C51.1 (p1), C55.2 (p2), C90.1 (p1), C91.1 (p1), C110.1 (p1), C111.1 (p1), C112.1 (p1), C113.1 (p1), Q2.3 (S), Q3.2 (D), R11.2 (p2), R51.1 (p1), R71.2 (p2), R95.1 (p1), R99.1 (p1), R101.1 (p1), T1.1 (p1), U18.2 (K); also elsewhere on the board
sw_b: C19.2 (p2), C20.1 (p1), C21.2 (p2), C22.2 (p2), C23.2 (p2), C57.1 (p1), C58.1 (p1), C62.2 (p2), C94.1 (p1), C95.1 (p1), C118.1 (p1), C119.1 (p1), C120.1 (p1), C121.1 (p1), C151.2 (p2), C152.2 (p2), Q5.3 (S), Q6.2 (D), R19.2 (p2), R25.2 (p2), R55.1 (p1), R74.2 (p2), R110.1 (p1), R114.1 (p1), R116.1 (p1), U20.2 (K); also elsewhere on the board
tco_l: J3.2 (p2), PS2.1 (p1)
u_bf_st-nc: U47.1 (NC)
u_bias_flt-nc: U40.1 (NC)
u_hot5_schmitt-nc: U15.1 (NC)
u_iso-nc2: U9.2 (p2)
u_iso-nc5: U9.5 (p5)
u_iso-nc6: U9.6 (p6)
u_iso-nc8: U9.8 (p8)
u_iso-nc10: U9.10 (p10)
u_iso-nc11: U9.11 (p11)
u_iso-nc12: U9.12 (p12)
u_iso-nc15: U9.15 (p15)
u_ldo-nc: U3.4 (NC)
u_ref-nc: U5.3 (NC)
v3v3: C7.1 (p1), C14.1 (p1), C29.1 (p1), C37.1 (p1), C44.1 (p1), C45.1 (p1), C46.1 (p1), C47.1 (p1), C54.1 (p1), C61.1 (p1), C89.1 (p1), C134.1 (p1), C144.1 (p1), C150.1 (p1), C153.1 (p1), C154.1 (p1), C155.1 (p1), C156.1 (p1), C163.1 (p1), C168.1 (p1), C169.1 (p1), C170.1 (p1), C171.1 (p1), C172.1 (p1), C173.1 (p1), C174.1 (p1), C175.1 (p1), C176.1 (p1), C177.1 (p1), C178.1 (p1), C179.1 (p1), D4.1 (K), J4.3 (V3V3_FROM_CONTROLLER), R40.1 (p1), R43.1 (p1), R45.1 (p1), R73.1 (p1), R76.1 (p1), R125.1 (p1), U1.3 (p3), U1.8 (p8), U2.3 (p3), U2.8 (p8), U4.8 (VDD2), U9.14 (p14), U10.5 (VCC), U11.5 (VCC), U12.5 (VCC), U13.5 (VCC), U22.5 (p5), U23.5 (p5), U24.5 (VCC), U32.14 (p14), U40.5 (VCC), U46.5 (p5), U47.5 (VCC); also elsewhere on the board
v15_ls: C8.1 (p1), C9.1 (p1), C15.1 (p1), C16.1 (p1), C24.1 (p1), C25.1 (p1), C65.1 (p1), C70.1 (p1), C99.1 (p1), C100.1 (p1), C131.1 (p1), C146.1 (p1), C148.1 (p1), R59.1 (p1), R72.1 (p1), R75.1 (p1), R85.1 (p1), R87.1 (p1), R136.1 (p1), R138.1 (p1), U1.11 (p11), U2.11 (p11), U3.1 (IN), U26.1 (p1), U26.3 (p3), U26.20 (p20), U29.3 (VCC), U37.1 (IN); also elsewhere on the board
v24_raw: C74.1 (p1), C81.1 (p1), C98.1 (p1), C102.1 (p1), C103.1 (p1), C105.1 (p1), C106.1 (p1), C107.1 (p1), C109.1 (p1), PS2.4 (p4), R62.1 (p1), R128.1 (p1), U26.13 (p13), U26.15 (p15), U26.16 (p16), U41.6 (p6), U41.7 (p7), U42.6 (p6), U42.7 (p7); also elsewhere on the board
vbus_n: J4.12 (p12), U4.6 (VOUTN)
vbus_p: J4.11 (p11), U4.7 (VOUTP)
vdiv_1: R26.2 (p2), R27.1 (p1)
vdiv_2: R27.2 (p2), R28.1 (p1)
vdiv_3: R28.2 (p2), R29.1 (p1)
vote_b_nc: D20.1 (p1)
vote_nc: D18.2 (p2)
vsense_in: C27.1 (p1), R29.2 (p2), R30.1 (p1), U4.2 (VINP), U7.4 (INN)
xbleed_mid: R1.2 (p2), R2.1 (p1)

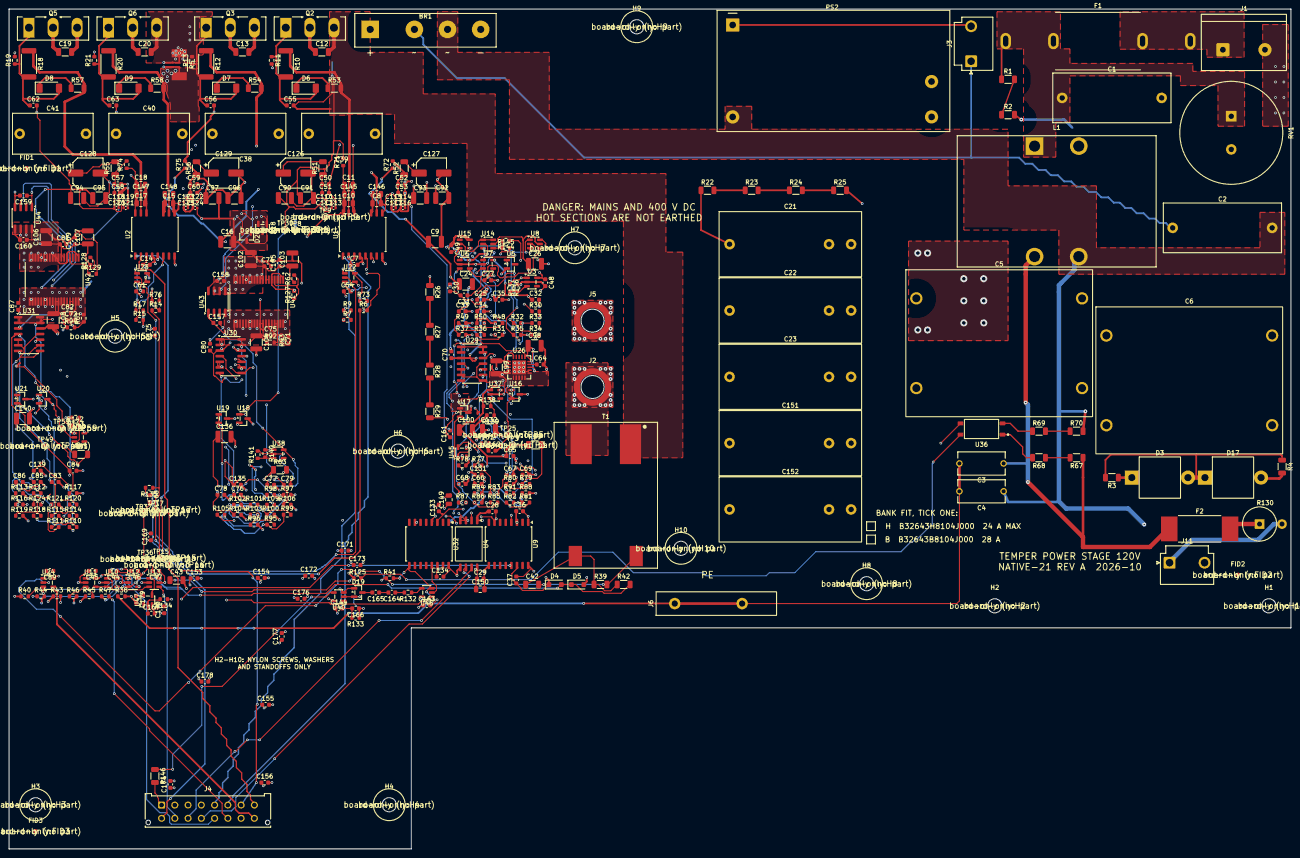
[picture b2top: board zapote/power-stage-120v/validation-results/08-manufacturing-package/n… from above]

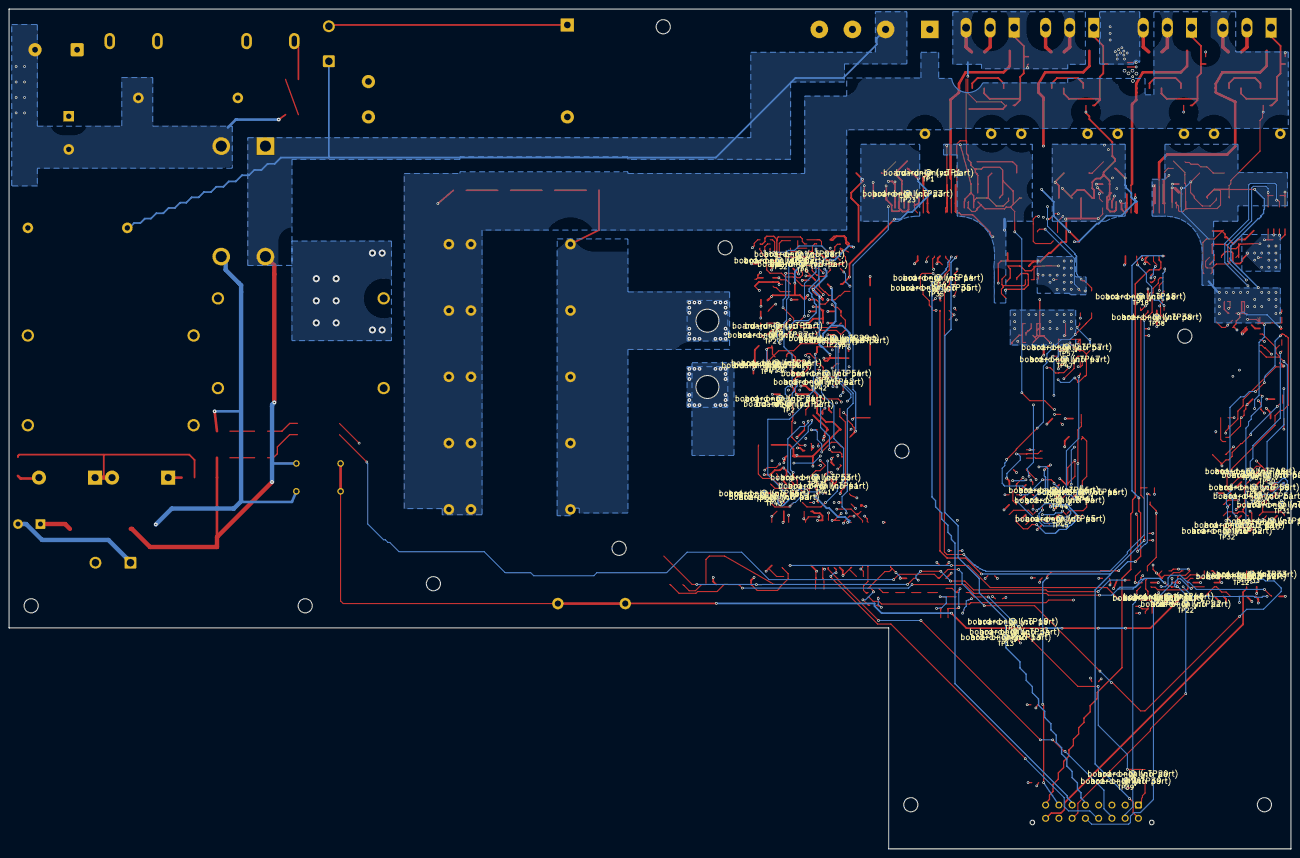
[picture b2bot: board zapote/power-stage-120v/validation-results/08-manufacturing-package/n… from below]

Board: 4 copper layers, 290.0 x 190.0 mm, 446 parts (47 on the bottom side), 145 nets.

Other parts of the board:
FID1, FID2, FID3: FIDUCIAL; Fiducial_1mm_Mask3mm
H1, H2: M3; MountingHole_3.2mm_M3
H3, H4, H5, H6, H7, H8, H9, H10: M3 NYLON ONLY; MountingHole_3.2mm_M3
TP1: leg_a-out_l; TestPoint_Pad_D1.0mm
TP2, TP23, TP26, TP53, TP54, TP55: n_ls; TestPoint_Pad_D1.0mm
TP3: v15_ls; TestPoint_Pad_D1.0mm
TP4: v24_raw; TestPoint_Pad_D1.0mm
TP5: ocp_node; TestPoint_Pad_D1.0mm
TP6: hot5; TestPoint_Pad_D1.0mm
TP7: bus_fault_hot; TestPoint_Pad_D1.0mm
TP8, TP56, TP57: n_ha; TestPoint_Pad_D1.0mm
TP9: p_ha; TestPoint_Pad_D1.0mm
TP10, TP58, TP59: n_hb; TestPoint_Pad_D1.0mm
TP11: p_hb; TestPoint_Pad_D1.0mm
TP12: v3v3; TestPoint_Pad_D1.0mm
TP13: pwm_ha; TestPoint_Pad_D1.0mm
TP14: pwm_la; TestPoint_Pad_D1.0mm
TP15: pwm_hb; TestPoint_Pad_D1.0mm
TP16: pwm_lb; TestPoint_Pad_D1.0mm
TP17: permit; TestPoint_Pad_D1.0mm
TP18: leg_b-driver_dis; TestPoint_Pad_D1.0mm
TP19: bias_good; TestPoint_Pad_D1.0mm
TP20: bus_fault; TestPoint_Pad_D1.0mm
TP21: ct_zc; TestPoint_Pad_D1.0mm
TP22: ct_mon; TestPoint_Pad_D1.0mm
TP24, TP25: leg_ret; TestPoint_Pad_D1.0mm
TP27, TP28, TP29: ocp_kelvin_p; TestPoint_Pad_D1.0mm
TP30: sw_a; TestPoint_Pad_D1.0mm
TP31, TP32: sw_b; TestPoint_Pad_D1.0mm
TP33, TP34, TP35, TP36, TP37, TP38, TP39, TP40: selv_gnd; TestPoint_Pad_D1.0mm
TP41: monitor_ls-uv; TestPoint_Pad_D1.0mm
TP42: monitor_ls-spanuv; TestPoint_Pad_D1.0mm
TP43: monitor_ls-spanov; TestPoint_Pad_D1.0mm
TP44: bias_ha.monitor-uv; TestPoint_Pad_D1.0mm
TP45: bias_ha.monitor-ov; TestPoint_Pad_D1.0mm
TP46: bias_ha.monitor-spanuv; TestPoint_Pad_D1.0mm
TP47: bias_ha.monitor-spanov; TestPoint_Pad_D1.0mm
TP48: bias_hb.monitor-uv; TestPoint_Pad_D1.0mm
TP49: bias_hb.monitor-ov; TestPoint_Pad_D1.0mm
TP50: bias_hb.monitor-spanuv; TestPoint_Pad_D1.0mm
TP51: bias_hb.monitor-spanov; TestPoint_Pad_D1.0mm
TP52: ref25; TestPoint_Pad_D1.0mm

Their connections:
bias_good: TP19.1; also elsewhere on the board
bias_ha.monitor-ov: TP45.1; also elsewhere on the board
bias_ha.monitor-spanov: TP47.1; also elsewhere on the board
bias_ha.monitor-spanuv: TP46.1; also elsewhere on the board
bias_ha.monitor-uv: TP44.1; also elsewhere on the board
bias_hb.monitor-ov: TP49.1; also elsewhere on the board
bias_hb.monitor-spanov: TP51.1; also elsewhere on the board
bias_hb.monitor-spanuv: TP50.1; also elsewhere on the board
bias_hb.monitor-uv: TP48.1; also elsewhere on the board
bus_fault: TP20.1; also elsewhere on the board
bus_fault_hot: TP7.1; also elsewhere on the board
ct_mon: TP22.1; also elsewhere on the board
ct_zc: TP21.1; also elsewhere on the board
hot5: TP6.1; also elsewhere on the board
leg_a-out_l: TP1.1; also elsewhere on the board
leg_b-driver_dis: TP18.1; also elsewhere on the board
leg_ret: TP24.1, TP25.1; also elsewhere on the board
monitor_ls-spanov: TP43.1; also elsewhere on the board
monitor_ls-spanuv: TP42.1; also elsewhere on the board
monitor_ls-uv: TP41.1; also elsewhere on the board
n_ha: TP8.1, TP56.1, TP57.1; also elsewhere on the board
n_hb: TP10.1, TP58.1, TP59.1; also elsewhere on the board
n_ls: TP2.1, TP23.1, TP26.1, TP53.1, TP54.1, TP55.1; also elsewhere on the board
ocp_kelvin_p: TP27.1, TP28.1, TP29.1; also elsewhere on the board
ocp_node: TP5.1; also elsewhere on the board
p_ha: TP9.1; also elsewhere on the board
p_hb: TP11.1; also elsewhere on the board
permit: TP17.1; also elsewhere on the board
pwm_ha: TP13.1; also elsewhere on the board
pwm_hb: TP15.1; also elsewhere on the board
pwm_la: TP14.1; also elsewhere on the board
pwm_lb: TP16.1; also elsewhere on the board
ref25: TP52.1; also elsewhere on the board
selv_gnd: TP33.1, TP34.1, TP35.1, TP36.1, TP37.1, TP38.1, TP39.1, TP40.1; also elsewhere on the board
sw_a: TP30.1; also elsewhere on the board
sw_b: TP31.1, TP32.1; also elsewhere on the board
v3v3: TP12.1; also elsewhere on the board
v15_ls: TP3.1; also elsewhere on the board
v24_raw: TP4.1; also elsewhere on the board

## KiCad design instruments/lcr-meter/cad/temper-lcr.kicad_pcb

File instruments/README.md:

# instruments

Bench instruments built alongside Temper, and the code they share.  Each instrument lives on its own branch
until it lands; shared code lives here so every instrument branch picks it up from main.

| path | what |
|---|---|
| [boardkit](boardkit/) | `temper-boardkit`: PCB craft passes, pre-DRC, Gerber/JLC DFM checks, pcbnew helpers (Python 3.9+) for the hand-routed instrument boards |

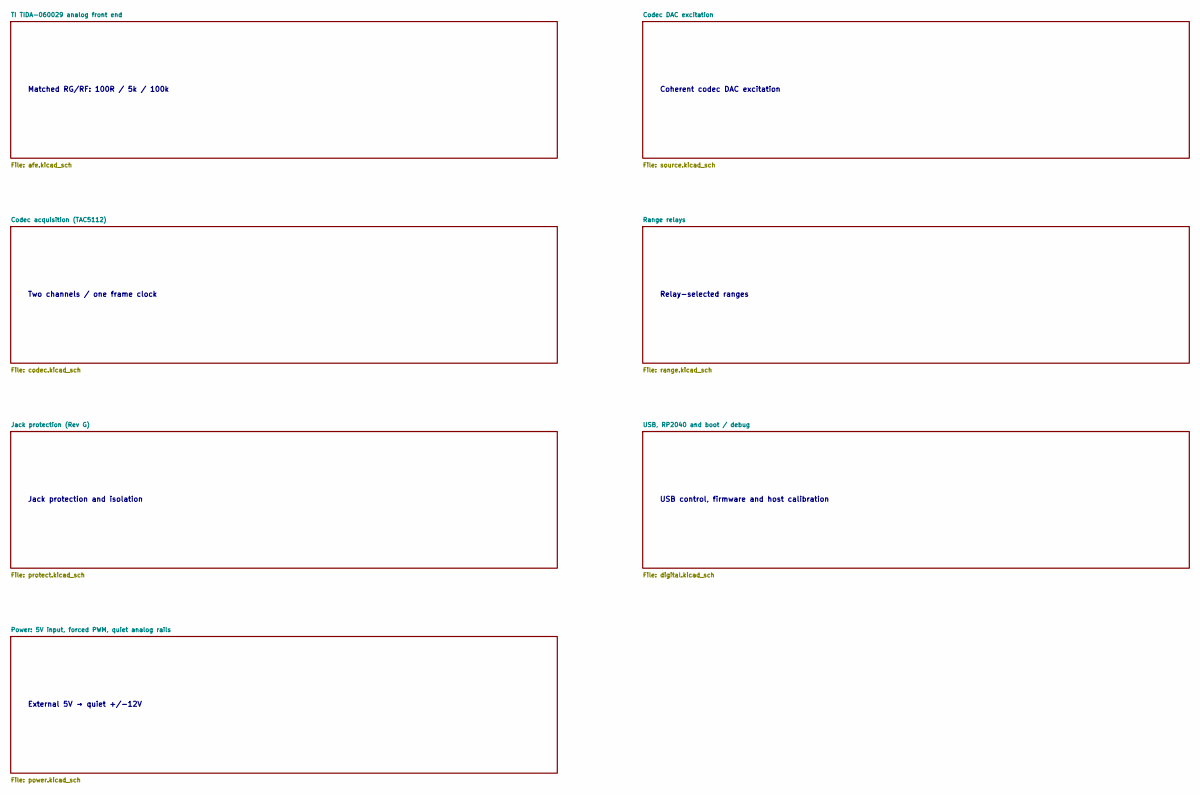
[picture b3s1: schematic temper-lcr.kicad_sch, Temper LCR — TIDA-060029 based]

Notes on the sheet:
Matched RG/RF: 100R / 5k / 100k
Coherent codec DAC excitation
Two channels / one frame clock
Relay-selected ranges
Jack protection and isolation
USB control, firmware and host calibration
External 5V → quiet +/-12V
